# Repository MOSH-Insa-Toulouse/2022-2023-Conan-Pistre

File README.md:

# 2022-2023-Conan-Pistre

Ce projet s'inscrit dans l'UF "*Du capteur au banc de Test*". Il consiste en l'élaboration d'un capteur de déformation/Jauge de contrainte à base de graphite.
**Design**, **Conception**, **Test** et **Codage** de notre Capteur et de son circuit sont détaillés ci-dessous.

## Descriptif du Projet

Notre projet se sépare en deux axes précis:
 - Le développement d'une partie *Professionnelle* permettant depuis une application et un affichage OLED d'obtenir les valeurs de résistance de notre capteur
 - Le développement d'une partie *Fun* permettant une application pratique du capteur pour jouer au Dino Game de google.

## Sommaire

* [Tests et Mesures LTSpice : circuit amplificateur Transimpédance à deux étages](#PremiereSection)
* [Fabrication du Shield](#DeuxiemeSection)
  * [Composants designés : Symboles & empreintes](#DeuxiemeSection1)
  * [Schématique](#DeuxiemeSection2)
  * [Placement des composants](#DeuxiemeSection3)
  * [Réalisation du PCB](#DeuxiemeSection4)
  * [Perçage et soudure](#DeuxiemeSection5)
* [Code Arduino](#TroisiemeSection)
  * [Lecture de la valeur de la Résistance](#TroisiemeSection1)
  * [Gestion du BlueTooth](#TroisiemeSection2)
  * [Gestion de l'affichage OLED](#TroisiemeSection3)
* [Application Smartphone APK](#QuatriemeSection)
* [Banc de test](#CinquiemeSection)
* [Datasheet](#SixiemeSection)

## Tests et Mesures LTSpice : circuit amplificateur Transimpédance à deux étages 

Les tests suivants ont été réalisés sur LTSpice 17.00.27.00 Le Schéma du circuit `ci-dessous` représente le circuit choisi pour optimiser les capacités de notre capteur. En effet ce dernier possédant une résistance élevée, il ne délivrera qu'un courant faible qu'il nous faut amplifier pour obtenir des résultats exploitables par notre programme Arduino réalisé sur Arduino 1.8.19.

**Schéma électrique Optimisé**

Ce circuit possède 3 filtres ayant chacun leur utilité :
 - `en rouge` le filtre passe bas passif permet donc filtrer les perturbations et les excès de bruit en courant sur la forme du signal d'entrée, il possède une fréquence de coupure aux alentour de 16Hz.
 - `en vert` le filtre passe haut actif permet de supprimer la composante parasite de 50Hz qui vient perturber le signal, il possède une fréqence de 1,6Hz.
 - `en violet` le filtre passe bas passif permet limiter le bruit lors du traitement du signal, il possède une fréquence de 1,6kHz.

Passons maintenant à la simulation de notre circuit afin d'en évaluer l'optimisation :

**Vérification du la tension de sortie du montage avec un courant d'entrée égal à 100nA**

Comme constaté `ci-dessus` notre circuit permet bien un gain de 100dB ce qui permet une nette augmentation du signal de sortie par rapport au signal d'entrée.

## Fabrication du Shield 

Pour fabriquer notre PCB nous avons du le designer sur KICAD 7.0. Nous avons ajouté au circuit précédent un écran OLED, un encodeur rotatoire ainsi qu'un module Bluetooth afin d'exploiter les résultats de notre capteur.

### Composants designés : Symboles & empreintes 

* Ecran OLED 

* Module Bluetooth

* Amplificateur LT1050 

* Capteur Graphite 

* Encodeur Rotatoire

### Schématique 

Une fois les symboles et empreintes créés, nous avons réalisé le schéma de notre shield. En haut à gauche sont représentées les broches de la carte Arduino. Au milieu est représenté le cicuit comprenant notre capteur et l'amplificateur transimpédance et juste au-dessus se trouvent l'écran OLED, le module bluetooth et l'encodeur rotatoire.

### Placement des composants 

### Réalisation du PCB 

Le PCB a été réalisé avec l'aide de Cathy. Notre PCB a été fabriqué à partir d'une plaque d'Epoxy recouverte d'une fine couche de cuivre (≃ 60μm). Nous avons imprimé sur du papier calque la modélisation de notre PCB réalisée sur KICAD pour ensuite insoler notre plaquette aux UV avec le calque par-dessus pendant quelques minutes. À l'aide d'un révélateur, nous avons retiré la partie de la résine non insolée. La plaquette d'Epoxy est ensuite placée dans un bain de perchlorure de fer pour la gravure, cette opération dure en moyenne 7-9min. Le cuivre non protégé par la résine est ainsi retiré de la plaquette ce qui nous permet d'obtenir notre PCB correspondant à notre KICAD. Enfin, un rincage à l'acétone est réalisé sur la plaquette pour éliminer les dernières traces de résine.

### Perçage et soudure 

Nous avons ensuite percé notre PCB aux emplacements où les différents composants seront insérés à l'aide d'une perceuse électrique. Le diamètre des trous dépend des différents composants à placer :

⌀ 0.8mm : AOP LTC1050, résistances et capacités
⌀ 1.0mm : Broches de connexion de la carte Arduino Uno et headers des différents modules (OLED, bluetooth, encodeur rotatoire)

## Code Arduino 
### Lecture de la valeur de la Résistance 
### Gestion du BlueTooth 
### Gestion de l'affichage OLED 
## Application Smartphone APK 
## Banc de test 

Pour réaliser notre phase de test, nous avons utilisé le banc de test réalisé lors des années précédentes : 7 demi-cercles en plastique, dont les diamètres varient de 2cm à 5cm. Le test alors réalisé est plutôt simple : nous mesurons différentes valeurs de résistance en courbant notre capteur sur le banc de test. Nous utilisons 3 capteurs préparés à l'aide de 3 types de crayons différents à dureté variable : un HB, un 1B et un 4B.

Les résultats obtenus semblent cohérents. En effet, une mine 4B dépose plus de graphite qu'une mine 1B elle même plus généreuse qu'une mine HB. Le dépôt de graphite plus important entraine une résistance globale plus faible. Nos capteurs ont bien une résistance variable selon leur déformation comme attendus d'une jauge de contrainte. Petit bémol cependant à constater : l'espérance de vie du capteur est très faible, après la série de tests il n'est déjà quasi plus utilisable. Cela réduit bien evidemment ses chances d'utilisation à grande échelle.

## Datasheet

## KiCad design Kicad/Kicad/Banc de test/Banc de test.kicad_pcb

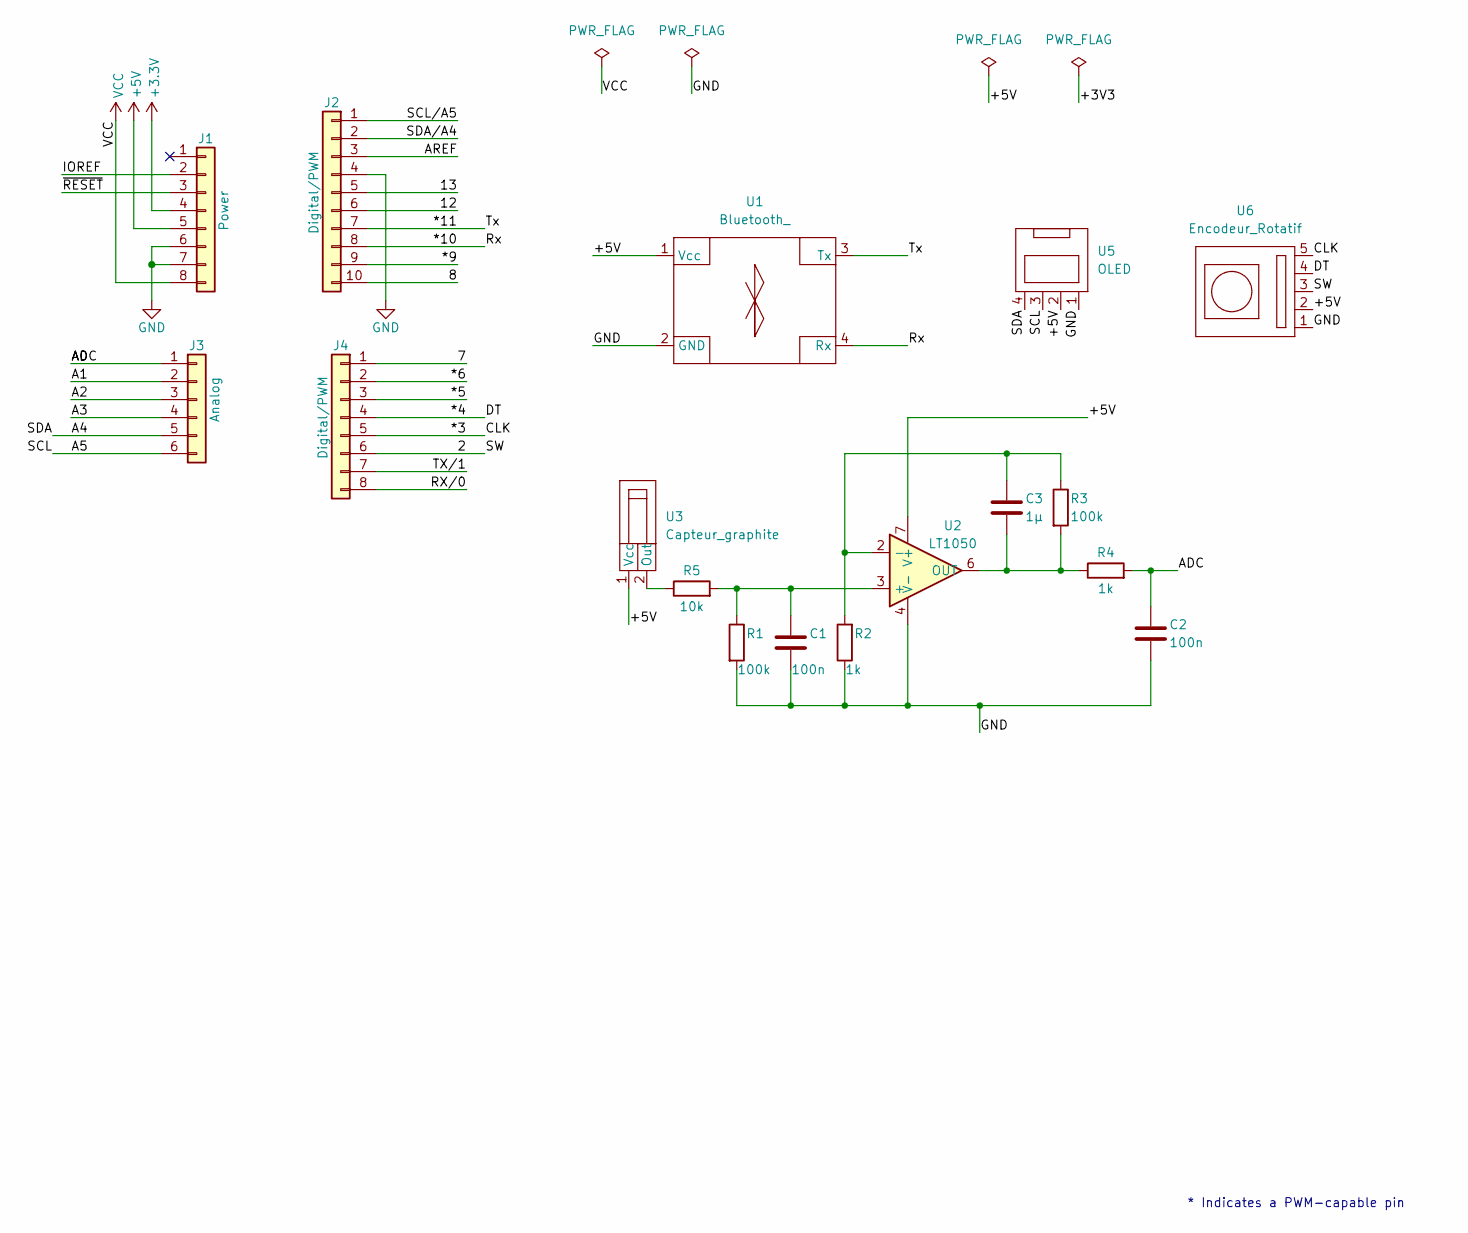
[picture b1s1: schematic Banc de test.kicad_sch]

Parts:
C1, C2: 100n; C_Disc_D5.0mm_W2.5mm_P5.00mm
C3: 1µ; C1uK63
J1: Power; PinSocket_1x08_P2.54mm_Vertical
J2: Digital/PWM; PinSocket_1x10_P2.54mm_Vertical
J3: Analog; PinSocket_1x06_P2.54mm_Vertical
J4: Digital/PWM; PinSocket_1x08_P2.54mm_Vertical
R1, R3: 100k; R_Axial_DIN0207_L6.3mm_D2.5mm_P10.16mm_Horizontal
R2, R4: 1k; R_Axial_DIN0207_L6.3mm_D2.5mm_P10.16mm_Horizontal
R5: 10k; R_Axial_DIN0207_L6.3mm_D2.5mm_P10.16mm_Horizontal
U1: Bluetooth_; Bluetooth_Empreinte
U2: LT1050; LTC1050
U3: Capteur_graphite; Graphite
U5: OLED
U6: Encodeur_Rotatif; Encodeur

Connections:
+3V3: J1.4
+5V: J1.5, U1.1 (Vcc), U2.7 (V+), U3.1 (Vcc), U5.2, U6.2
/2: J4.6, U6.3
/7: J4.1
/8: J2.10
/12: J2.6
/13: J2.5
/*3: J4.5, U6.5
/*4: J4.4, U6.4
/*5: J4.3
/*6: J4.2
/*9: J2.9
/*10: J2.8, U1.4 (Rx)
/*11: J2.7, U1.3 (Tx)
/A0: C2.2, J3.1, R4.2
/A1: J3.2
/A2: J3.3
/A3: J3.4
/A4: J3.5, U5.4
/A5: J3.6, U5.3
/AREF: J2.3
/IOREF: J1.2
/RX/0: J4.8
/SCL/A5: J2.1
/SDA/A4: J2.2
/TX/1: J4.7
/~RESET: J1.3
GND: C1.1, C2.1, J1.6, J1.7, J2.4, R1.2, R2.1, U1.2 (GND), U2.4 (V-), U5.1, U6.1
unnamed: C1.2, R1.1, R5.2, U2.3 (+)
unnamed: C3.1, R3.2, R4.1, U2.6 (OUT)
unnamed: C3.2, R2.2, R3.1, U2.2 (-)
unnamed: R5.1, U3.2 (Out)
VCC: J1.8

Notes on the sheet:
* Indicates a PWM-capable pin

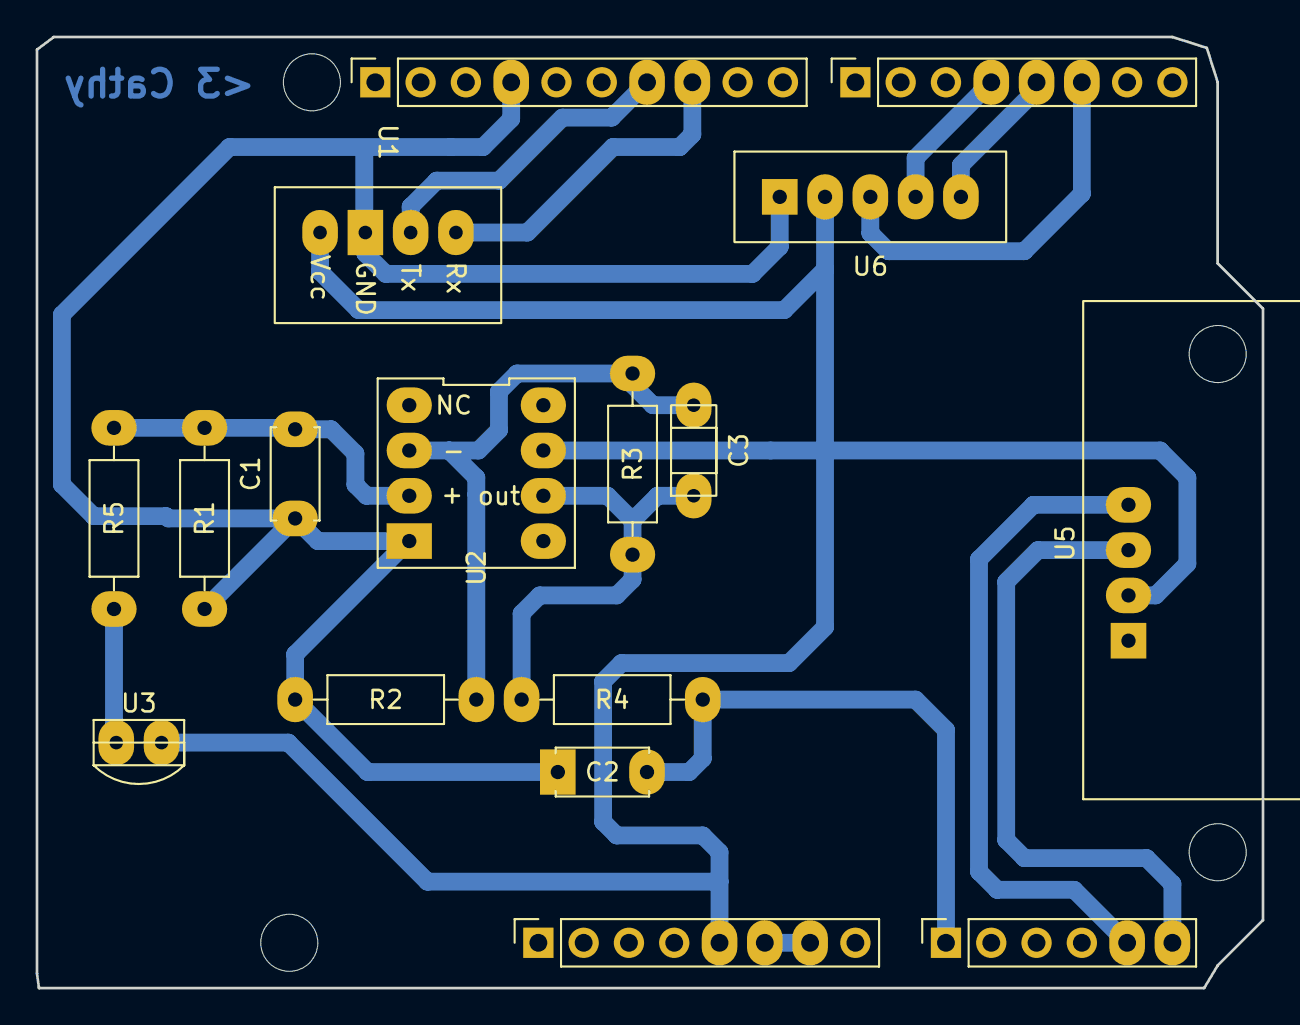
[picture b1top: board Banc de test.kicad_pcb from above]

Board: 2 copper layers, 68.8 x 53.3 mm, 21 parts (0 on the bottom side), 14 nets.

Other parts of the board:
MH1, MH2, MH3, MH4: MountingHole_3.2mm
